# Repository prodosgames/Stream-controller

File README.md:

# Salvador's Pad

Salvador's HackPad was designed to be useful in a variety of ways.

## Features:
- 6 buttons for whatever you need.
- 4 LEDs that might function as key illumination

## CAD Model:

## PCB
Here's my PCB! It was made in KiCad. It was Hard

Schematic

PCB

## BOM:
Here should be everything you need to make this hackpad

- 6x Cherry MX Switches
- 6x  Keycaps
- 4x M3x5x4 Heatset inserts
- 4x M3x16mm 
- 4x SK6812 MINI-E LEDs
- 1x XIAO RP2040
- 1x Case (2 printed parts)

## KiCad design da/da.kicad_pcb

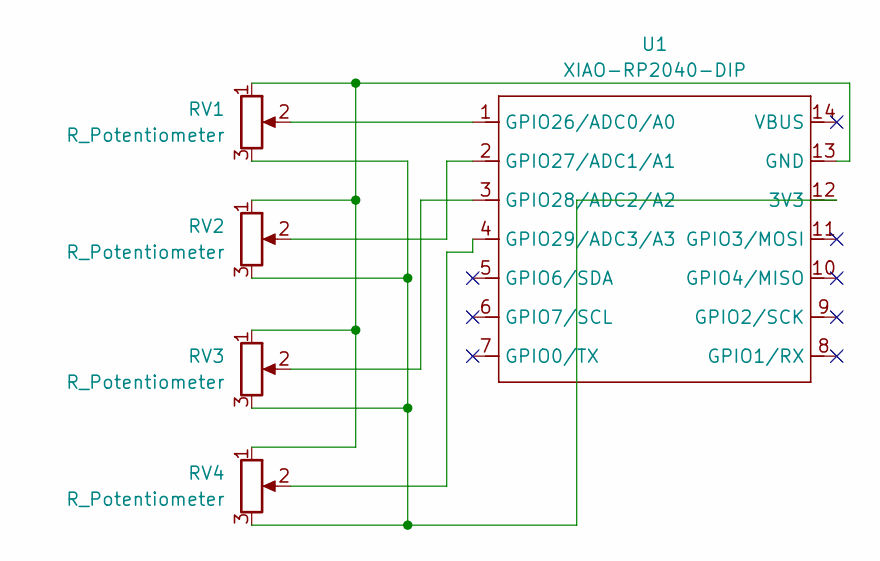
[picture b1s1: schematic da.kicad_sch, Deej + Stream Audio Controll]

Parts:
RV1, RV2, RV3, RV4: R_Potentiometer; Potentiometer_Bourns_PTV09A-2_Single_Horizontal
U1: XIAO-RP2040-DIP

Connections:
unnamed: RV1.3, RV2.3, RV3.3, RV4.3, U1.12 (3V3)
unnamed: RV1.1, RV2.1, RV3.1, RV4.1, U1.13 (GND)
unnamed: RV1.2, U1.1 (GPIO26/ADC0/A0)
unnamed: RV2.2, U1.2 (GPIO27/ADC1/A1)
unnamed: RV3.2, U1.3 (GPIO28/ADC2/A2)
unnamed: RV4.2, U1.4 (GPIO29/ADC3/A3)

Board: 2 copper layers, 5 parts (0 on the bottom side), 6 nets, no tracks yet.

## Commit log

2026-01-06 Added my v1 version
2026-01-10 Updated for final version
2026-01-10 Add author name to README.md
2026-01-11 Enhance README with HackPad details
    Added detailed information about features, CAD model, PCB, and BOM for Salvador's HackPad.
2026-01-15 Add CAD model image to README
    Added an image of the CAD model to the README.
